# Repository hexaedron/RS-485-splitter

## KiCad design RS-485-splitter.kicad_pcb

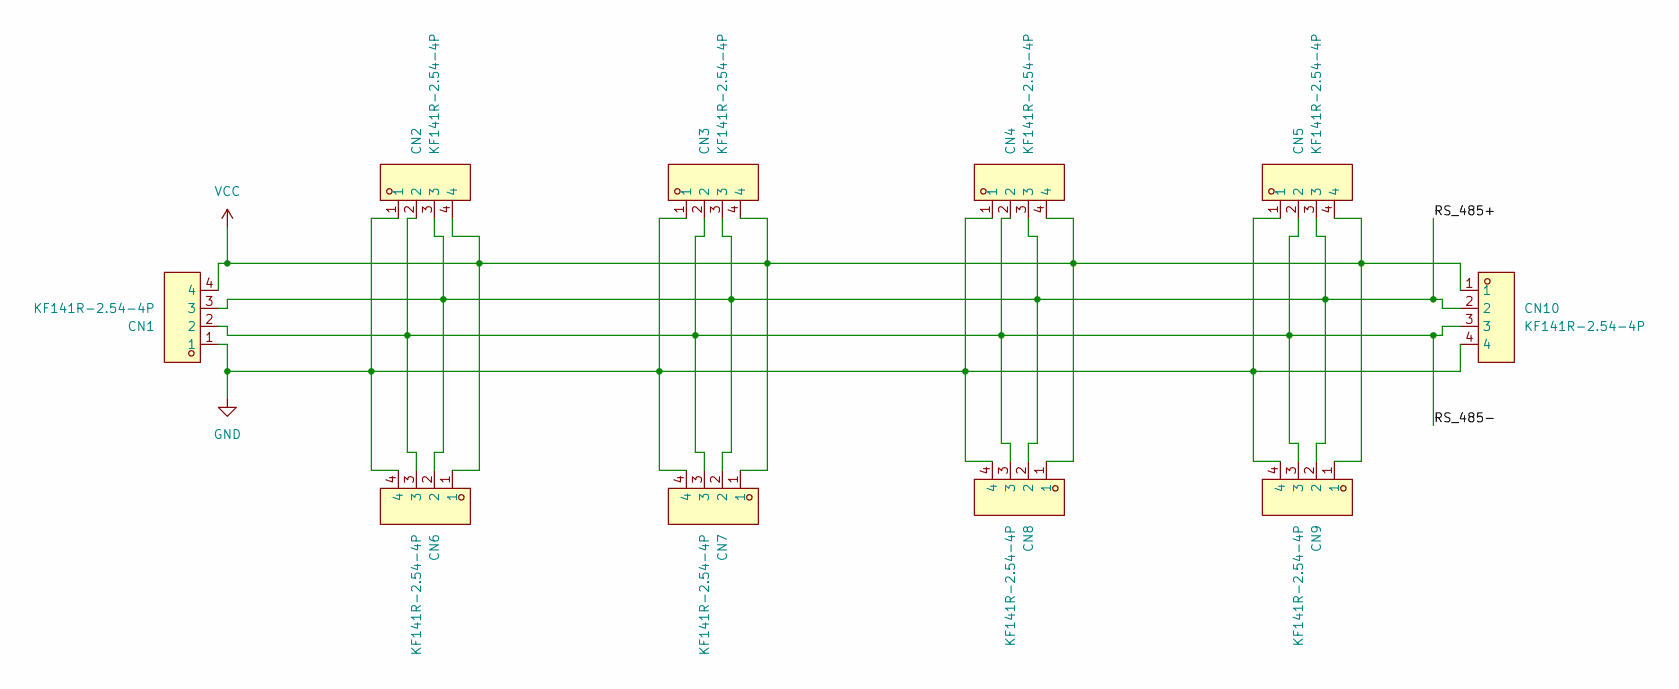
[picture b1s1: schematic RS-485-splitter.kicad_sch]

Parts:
CN1, CN2, CN3, CN4, CN5, CN6, CN7, CN8, CN9, CN10: KF141R-2.54-4P; CONN-TH_4P-P2.54_KF141R-2.54-4P; MPN KF141R-2.54-4P; LCSC Part C475126

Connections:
/RS_485+: CN1.3, CN2.3, CN3.3, CN4.3, CN5.3, CN6.2, CN7.2, CN8.2, CN9.2, CN10.2
/RS_485-: CN1.2, CN2.2, CN3.2, CN4.2, CN5.2, CN6.3, CN7.3, CN8.3, CN9.3, CN10.3
GND: CN1.1, CN2.1, CN3.1, CN4.1, CN5.1, CN6.4, CN7.4, CN8.4, CN9.4, CN10.4
VCC: CN1.4, CN2.4, CN3.4, CN4.4, CN5.4, CN6.1, CN7.1, CN8.1, CN9.1, CN10.1

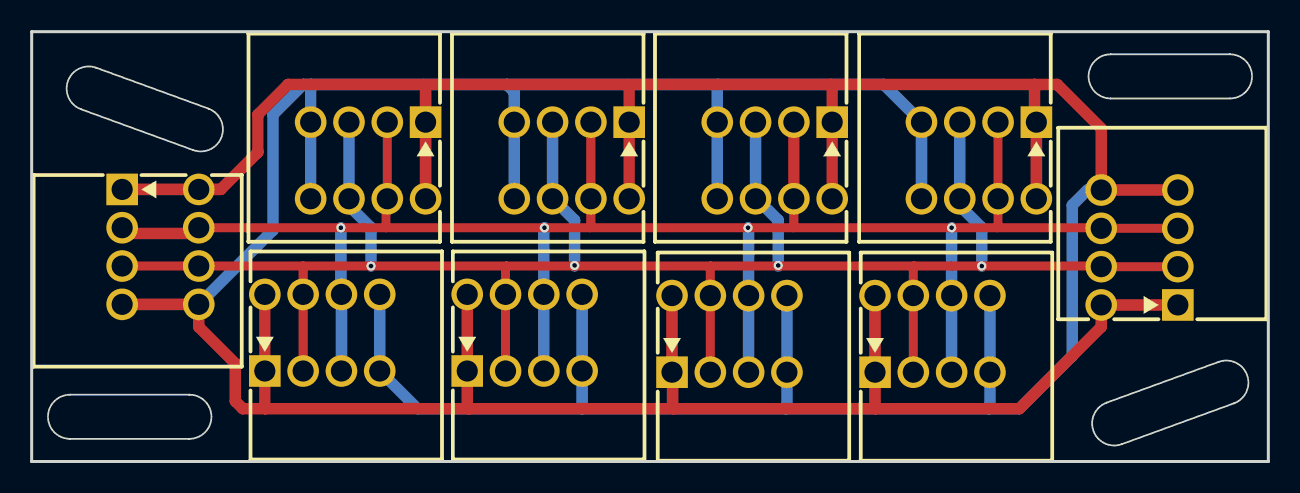
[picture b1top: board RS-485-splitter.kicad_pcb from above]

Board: 2 copper layers, 82.0 x 28.5 mm, 10 parts (0 on the bottom side), 4 nets.
